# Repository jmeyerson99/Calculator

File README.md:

# Calcular

An Open Source Graphing Calculator nicknamed "Calcular". Originally designed in C, being redesigned and simulated in Java.

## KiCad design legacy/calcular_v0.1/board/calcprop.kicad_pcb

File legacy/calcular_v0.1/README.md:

# Calcular
> Open-source graphing calculator, powered by a Parallax Propeller
> This is a legacy design. The new design is being simulated in Java, and implementing API calls to hardware before narrowing down the exact hardware required for implementation.
>> Allows for flexibility in features while designing. Minimum requirements are basic math, trig, log, graphing equations "y = "

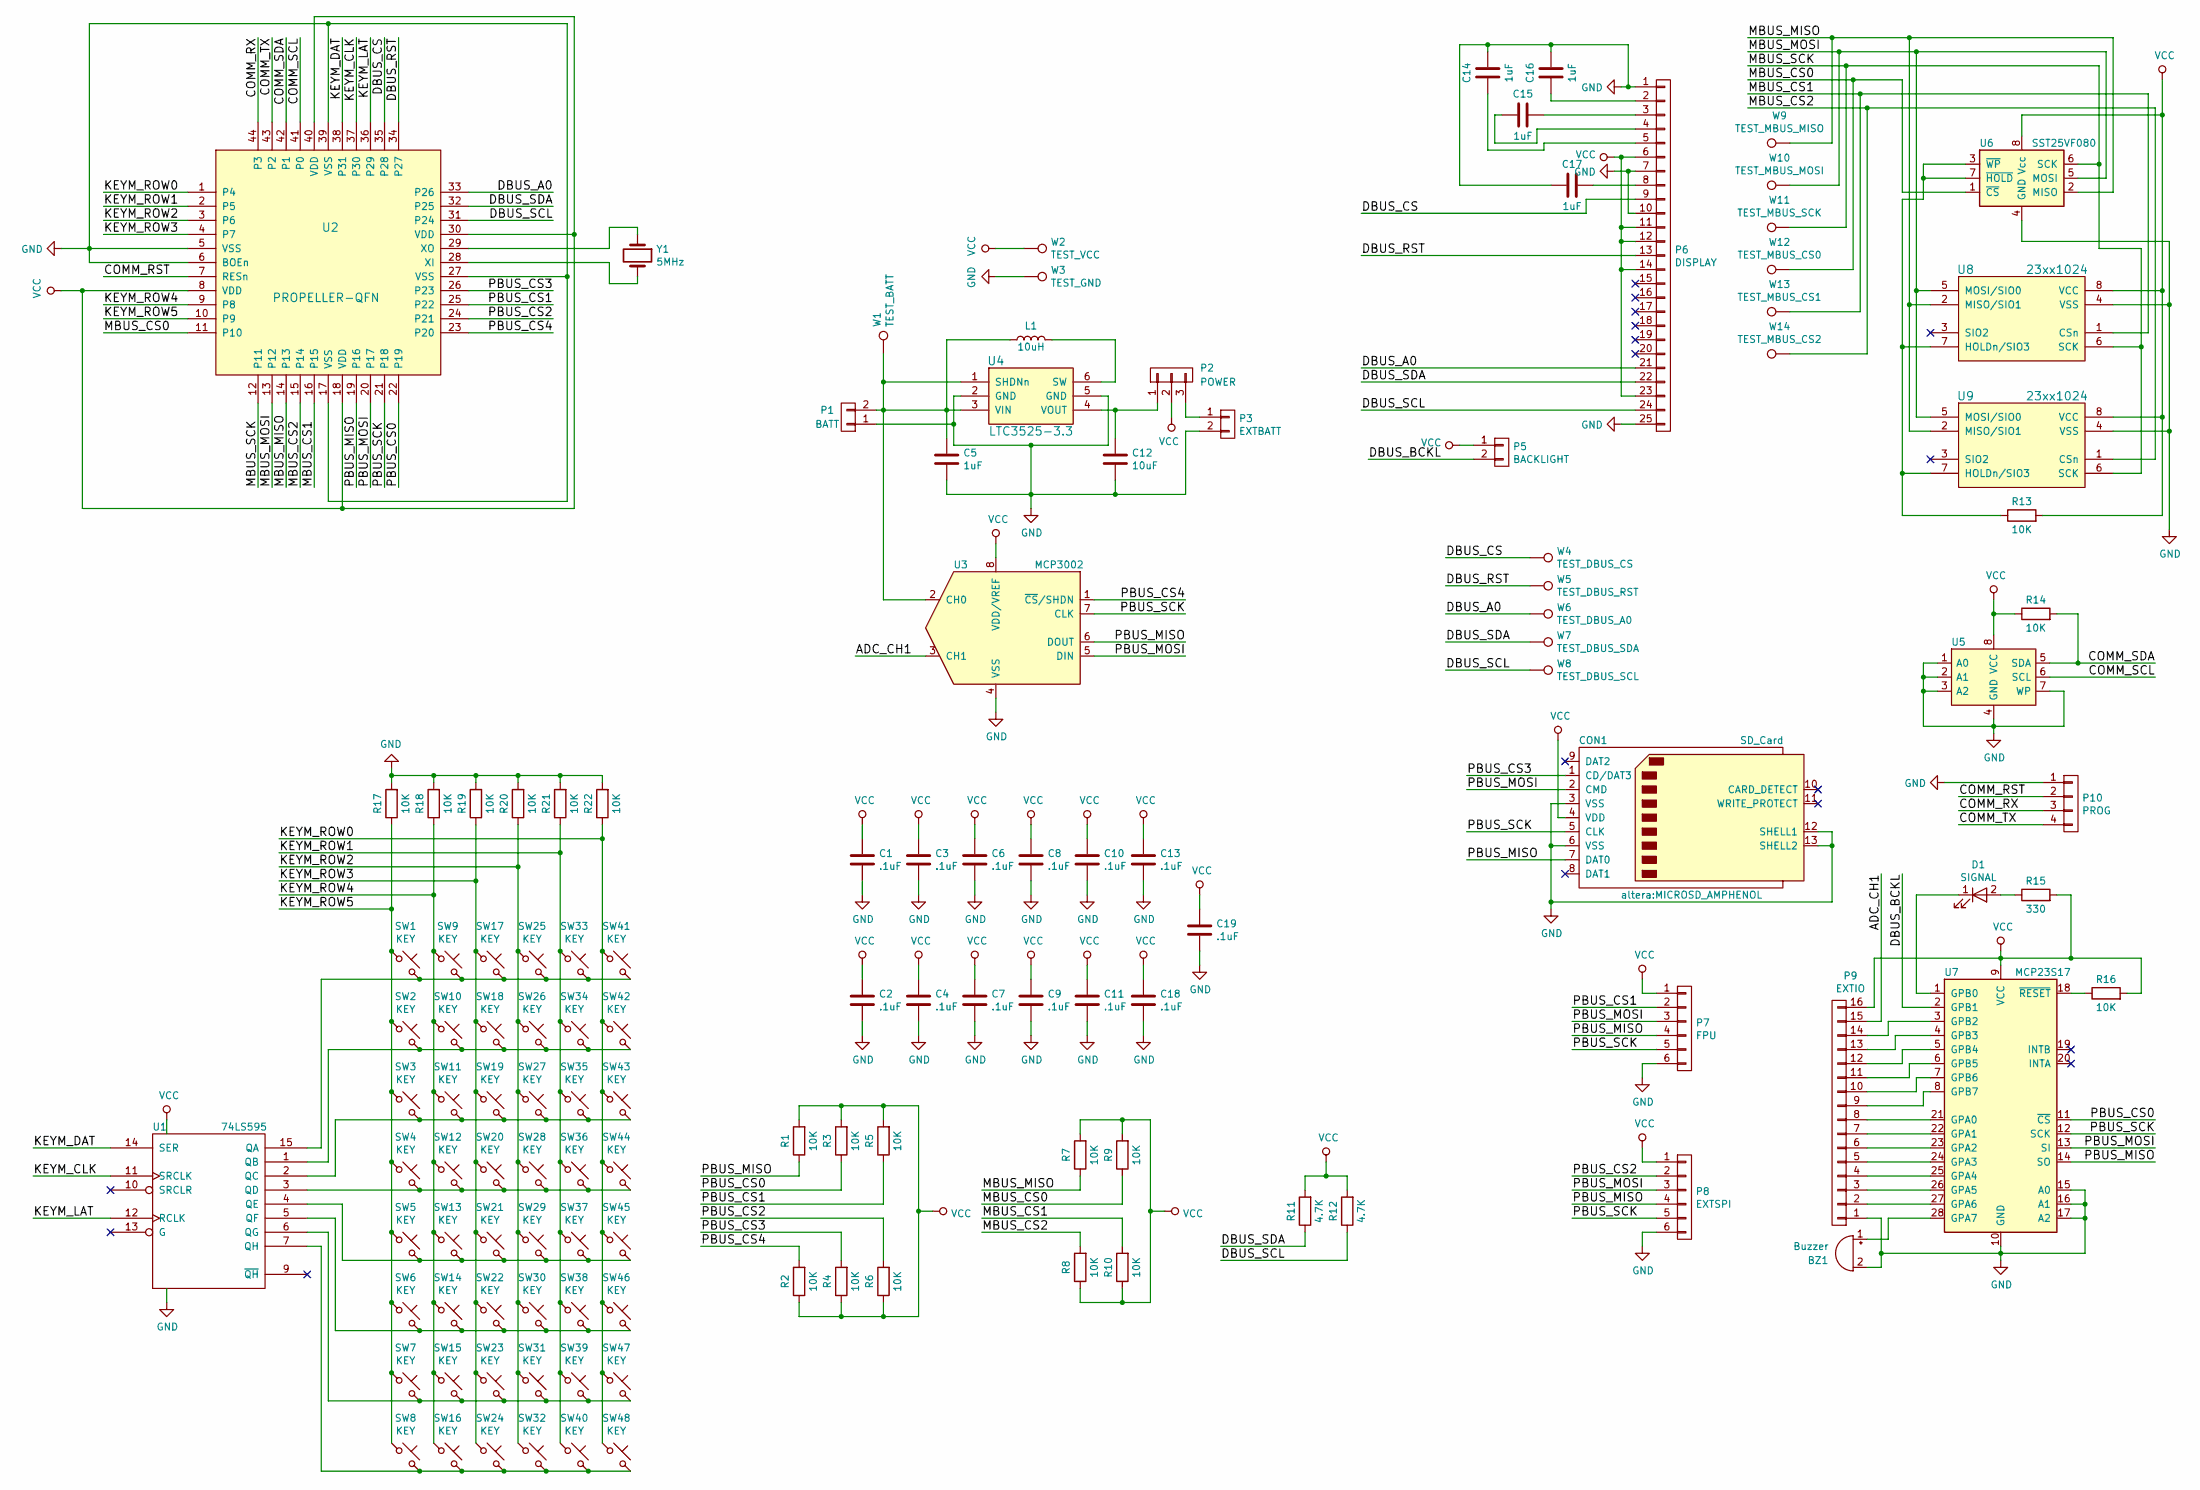
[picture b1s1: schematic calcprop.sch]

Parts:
BZ1: Buzzer; Pin_Header_Straight_1x02
C1, C2, C3, C4, C6, C7, C8, C9, C10, C11, C13, C18, C19: .1uF; C_0805
C5, C14, C15, C16, C17: 1uF; C_0805
C12: 10uF; C_0805
CON1: SD_Card; MICROSD_AMPHENOL
D1: SIGNAL; LED_1206
L1: 10uH; R_0805
P1: BATT; Pin_Header_Angled_1x02
P2: POWER; SW_SLIDE_PWR
P3: EXTBATT; Pin_Header_Straight_1x02
P5: BACKLIGHT; Pin_Header_Straight_1x02
P6: DISPLAY; ERC240160_FPC
P7: FPU; bb02-hp06
P8: EXTSPI; Socket_Strip_Angled_2x03
P9: EXTIO; Socket_Strip_Angled_2x08
P10: PROG; Pin_Header_Angled_1x04
R1, R2, R3, R4, R5, R6, R7, R8, R9, R10, R13, R14, R16, R17, R18, R19, R20, R21, R22: 10K; R_0805
R11, R12: 4.7K; R_0805
R15: 330; R_0805
SW1, SW2, SW3, SW4, SW5, SW6, SW7, SW8, SW9, SW10, SW11, SW12, SW13, SW14, SW15, SW16, SW17, SW18, SW19, SW20, SW21, SW22, SW23, SW24, SW25, SW26, SW27, SW28, SW29, SW30, SW31, SW32, SW33, SW34, SW35, SW36, SW37, SW38, SW39, SW40, SW41, SW42, SW43, SW44, SW45, SW46, SW47, SW48: KEY; SW_PUSH_SMALL
U1: 74LS595; SOIC-16_3.9x9.9mm_Pitch1.27mm
U2: PROPELLER-QFN; LQFP-44_10x10mm_Pitch0.8mm
U3: MCP3002; SOIC-8_3.9x4.9mm_Pitch1.27mm
U4: LTC3525-3.3; SC-70-6
U5: 24LC512; SOIC-8_3.9x4.9mm_Pitch1.27mm
U6: SST25VF080; SOIC-8-1EP_3.9x4.9mm_Pitch1.27mm
U7: MCP23S17; SOIC-28
U8, U9: 23xx1024; SOIC-8-1EP_3.9x4.9mm_Pitch1.27mm
W1: TEST_BATT; Measurement_Point_Round-SMD-Pad_Small
W2: TEST_VCC; Measurement_Point_Round-SMD-Pad_Small
W3: TEST_GND; Measurement_Point_Round-SMD-Pad_Small
W4: TEST_DBUS_CS; Measurement_Point_Round-SMD-Pad_Small
W5: TEST_DBUS_RST; Measurement_Point_Round-SMD-Pad_Small
W6: TEST_DBUS_A0; Measurement_Point_Round-SMD-Pad_Small
W7: TEST_DBUS_SDA; Measurement_Point_Round-SMD-Pad_Small
W8: TEST_DBUS_SCL; Measurement_Point_Round-SMD-Pad_Small
W9: TEST_MBUS_MISO; Measurement_Point_Round-SMD-Pad_Small
W10: TEST_MBUS_MOSI; Measurement_Point_Round-SMD-Pad_Small
W11: TEST_MBUS_SCK; Measurement_Point_Round-SMD-Pad_Small
W12: TEST_MBUS_CS0; Measurement_Point_Round-SMD-Pad_Small
W13: TEST_MBUS_CS1; Measurement_Point_Round-SMD-Pad_Small
W14: TEST_MBUS_CS2; Measurement_Point_Round-SMD-Pad_Small
Y1: 5MHz; Crystal_HC49-SD_SMD

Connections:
/ADC_CH1: P9.15, U3.3 (CH1)
/COMM_RST: P10.2, U2.7 (RESn)
/COMM_RX: P10.3, U2.44 (P3)
/COMM_SCL: U2.41 (P0), U5.6 (SCL)
/COMM_SDA: R14.2, U2.42 (P1), U5.5 (SDA)
/COMM_TX: P10.4, U2.43 (P2)
/DBUS_A0: P6.21, U2.33 (P26), W6.1
/DBUS_BCKL: P5.2, U7.2 (GPB1)
/DBUS_CS: P6.9, U2.35 (P28), W4.1
/DBUS_RST: P6.13, U2.34 (P27), W5.1
/DBUS_SCL: P6.24, R12.1, U2.31 (P24), W8.1
/DBUS_SDA: P6.22, R11.1, U2.32 (P25), W7.1
/KEYM_CLK: U1.11 (SRCLK), U2.37 (P30)
/KEYM_DAT: U1.14 (SER), U2.38 (P31)
/KEYM_LAT: U1.12 (RCLK), U2.36 (P29)
/KEYM_ROW0: R22.1, SW41.1, SW42.1, SW43.1, SW44.1, SW45.1, SW46.1, SW47.1, SW48.1, U2.1 (P4)
/KEYM_ROW1: R21.1, SW33.1, SW34.1, SW35.1, SW36.1, SW37.1, SW38.1, SW39.1, SW40.1, U2.2 (P5)
/KEYM_ROW2: R20.1, SW25.1, SW26.1, SW27.1, SW28.1, SW29.1, SW30.1, SW31.1, SW32.1, U2.3 (P6)
/KEYM_ROW3: R19.1, SW17.1, SW18.1, SW19.1, SW20.1, SW21.1, SW22.1, SW23.1, SW24.1, U2.4 (P7)
/KEYM_ROW4: R18.1, SW9.1, SW10.1, SW11.1, SW12.1, SW13.1, SW14.1, SW15.1, SW16.1, U2.9 (P8)
/KEYM_ROW5: R17.1, SW1.1, SW2.1, SW3.1, SW4.1, SW5.1, SW6.1, SW7.1, SW8.1, U2.10 (P9)
/MBUS_CS0: R9.1, U2.11 (P10), U6.1 (~CS), W12.1
/MBUS_CS1: R10.2, U2.16 (P15), U8.1 (CSn), W13.1
/MBUS_CS2: R8.2, U2.15 (P14), U9.1 (CSn), W14.1
/MBUS_MISO: R7.1, U2.14 (P13), U6.2 (MISO), U8.2 (MISO/SIO1), U9.2 (MISO/SIO1), W9.1
/MBUS_MOSI: U2.13 (P12), U6.5 (MOSI), U8.5 (MOSI/SIO0), U9.5 (MOSI/SIO0), W10.1
/MBUS_SCK: U2.12 (P11), U6.6 (SCK), U8.6 (SCK), U9.6 (SCK), W11.1
/PBUS_CS0: R3.1, U2.22 (P19), U7.11 (~CS)
/PBUS_CS1: P7.2, R5.1, U2.25 (P22)
/PBUS_CS2: P8.2, R6.2, U2.24 (P21)
/PBUS_CS3: CON1.1 (CD/DAT3), R4.2, U2.26 (P23)
/PBUS_CS4: R2.2, U2.23 (P20), U3.1 (~CS~/SHDN)
/PBUS_MISO: CON1.7 (DAT0), P7.4, P8.4, R1.1, U2.19 (P16), U3.6 (DOUT), U7.14 (SO)
/PBUS_MOSI: CON1.2 (CMD), P7.3, P8.3, U2.20 (P17), U3.5 (DIN), U7.13 (SI)
/PBUS_SCK: CON1.5 (CLK), P7.5, P8.5, U2.21 (P18), U3.7 (CLK), U7.12 (SCK)
GND: BZ1.2 (+), C1.2, C2.2, C3.2, C4.2, C5.2, C6.2, C7.2, C8.2, C9.2, C10.2, C11.2, C12.2, C13.2, C14.1, C16.1, C17.2, C18.2, C19.2, CON1.3 (VSS), CON1.6 (VSS), CON1.12 (SHELL1), CON1.13 (SHELL2), P1.1, P3.2, P6.1, P6.7, P6.10, P6.25, P7.6, P8.6, P9.1, P10.1, R17.2, R18.2, R19.2, R20.2, R21.2, R22.2, U1.8 (GND), U2.5 (VSS), U2.6 (BOEn), U2.17 (VSS), U2.27 (VSS), U2.39 (VSS), U3.4 (VSS), U4.2 (GND), U4.5 (GND), U5.1 (A0), U5.2 (A1), U5.3 (A2), U5.4 (GND), U5.7 (WP), U6.4 (GND), U7.10 (GND), U7.15 (A0), U7.16 (A1), U7.17 (A2), U8.4 (VSS), U9.4 (VSS), W3.1
unnamed: BZ1.1 (-), U7.28 (GPA7)
unnamed: C5.1, L1.1, P1.2, U3.2 (CH0), U4.1 (SHDNn), U4.3 (VIN), W1.1
unnamed: C12.1, P2.1, U4.4 (VOUT)
unnamed: C14.2, P6.5
unnamed: C15.1, P6.3
unnamed: C15.2, P6.4
unnamed: C16.2, P6.2
unnamed: C17.1, P6.8
unnamed: D1.1 (K), U7.1 (GPB0)
unnamed: D1.2 (A), R15.1
unnamed: L1.2, U4.6 (SW)
unnamed: P2.3, P3.1
unnamed: P9.2, U7.27 (GPA6)
unnamed: P9.3, U7.26 (GPA5)
unnamed: P9.4, U7.25 (GPA4)
unnamed: P9.5, U7.24 (GPA3)
unnamed: P9.6, U7.23 (GPA2)
unnamed: P9.7, U7.22 (GPA1)
unnamed: P9.8, U7.21 (GPA0)
unnamed: P9.9, U7.8 (GPB7)
unnamed: P9.10, U7.7 (GPB6)
unnamed: P9.11, U7.6 (GPB5)
unnamed: P9.12, U7.5 (GPB4)
unnamed: P9.13, U7.4 (GPB3)
unnamed: P9.14, U7.3 (GPB2)
unnamed: R13.1, U6.3 (~WP), U6.7 (~HOLD), U8.7 (HOLDn/SIO3), U9.7 (HOLDn/SIO3)
unnamed: R16.1, U7.18 (~RESET)
unnamed: SW1.2, SW9.2, SW17.2, SW25.2, SW33.2, SW41.2, U1.15 (QA)
unnamed: SW2.2, SW10.2, SW18.2, SW26.2, SW34.2, SW42.2, U1.1 (QB)
unnamed: SW3.2, SW11.2, SW19.2, SW27.2, SW35.2, SW43.2, U1.2 (QC)
unnamed: SW4.2, SW12.2, SW20.2, SW28.2, SW36.2, SW44.2, U1.3 (QD)
unnamed: SW5.2, SW13.2, SW21.2, SW29.2, SW37.2, SW45.2, U1.4 (QE)
unnamed: SW6.2, SW14.2, SW22.2, SW30.2, SW38.2, SW46.2, U1.5 (QF)
unnamed: SW7.2, SW15.2, SW23.2, SW31.2, SW39.2, SW47.2, U1.6 (QG)
unnamed: SW8.2, SW16.2, SW24.2, SW32.2, SW40.2, SW48.2, U1.7 (QH)
unnamed: U2.28 (XI), Y1.2
unnamed: U2.29 (XO), Y1.1
VCC: C1.1, C2.1, C3.1, C4.1, C6.1, C7.1, C8.1, C9.1, C10.1, C11.1, C13.1, C18.1, C19.1, CON1.4 (VDD), P2.2, P5.1, P6.6, P6.11, P6.12, P6.14, P6.23, P7.1, P8.1, P9.16, R1.2, R2.1, R3.2, R4.1, R5.2, R6.1, R7.2, R8.1, R9.2, R10.1, R11.2, R12.2, R13.2, R14.1, R15.2, R16.2, U1.16 (VCC), U2.8 (VDD), U2.18 (VDD), U2.30 (VDD), U2.40 (VDD), U3.8 (VDD/VREF), U5.8 (VCC), U6.8 (Vcc), U7.9 (VCC), U8.8 (VCC), U9.8 (VCC), W2.1

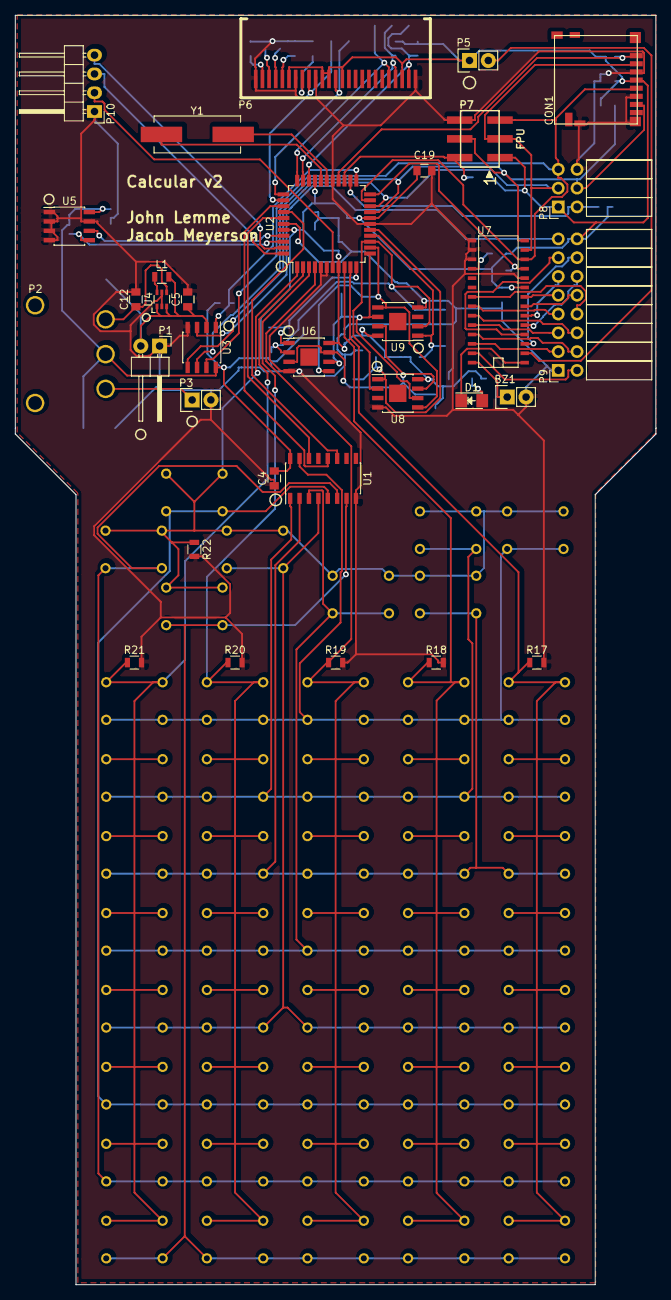
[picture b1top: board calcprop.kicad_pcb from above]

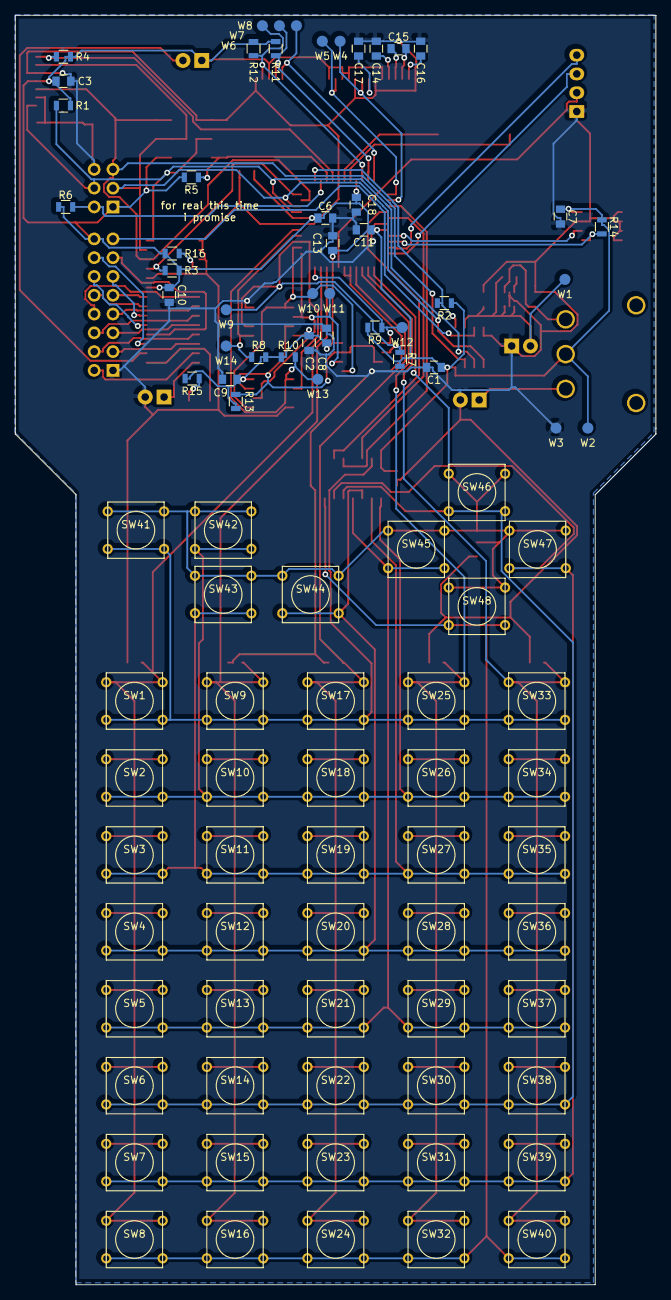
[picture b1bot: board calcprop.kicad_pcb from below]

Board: 2 copper layers, 86.6 x 171.6 mm, 126 parts (93 on the bottom side), 74 nets.

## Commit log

2018-12-19 Initial push
2018-12-20 Fixing some file issues
2018-12-20 Made a change
2018-12-20 Fixed 2nd mode button
2018-12-20 Added a gitignore
2018-12-20 Added architectural tiers
2018-12-28 New changes
2018-12-30 Added a parser for algebra and RPN
2019-01-01 Updated click handler
2019-01-02 Handle basic input
2019-01-03 Performs basic operations, updates display properly
2019-01-04 Can store values as variable X
2019-01-04 Updated bug with RPN Queue where removal of past commands did not work
2019-01-06 Fixed issue with parsing numbers larger than 1 digit
2019-08-17 First commit in a while
2019-08-29 Pushing from new desktop
2019-09-15 Updated comments
2020-05-22 Added support for writing pixels to display
2020-10-07 Cleaning up master branch
2020-10-07 Added Algebraic to RPN parsing tester
2020-10-07 Added blank README.md
2020-10-07 Added files
2020-10-07 Added legacy folder
2020-10-07 Restructured directory. Next step is checking files and function calls
2020-10-07 Added gitignore and prototyping directory
2020-10-07 Added gitignore and updated blanket package directories
